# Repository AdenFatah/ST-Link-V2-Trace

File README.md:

# ST-Link-V2-Trace
ST-Link V2 Clone Hardware expanded for Trace Support (SWV/SWO)

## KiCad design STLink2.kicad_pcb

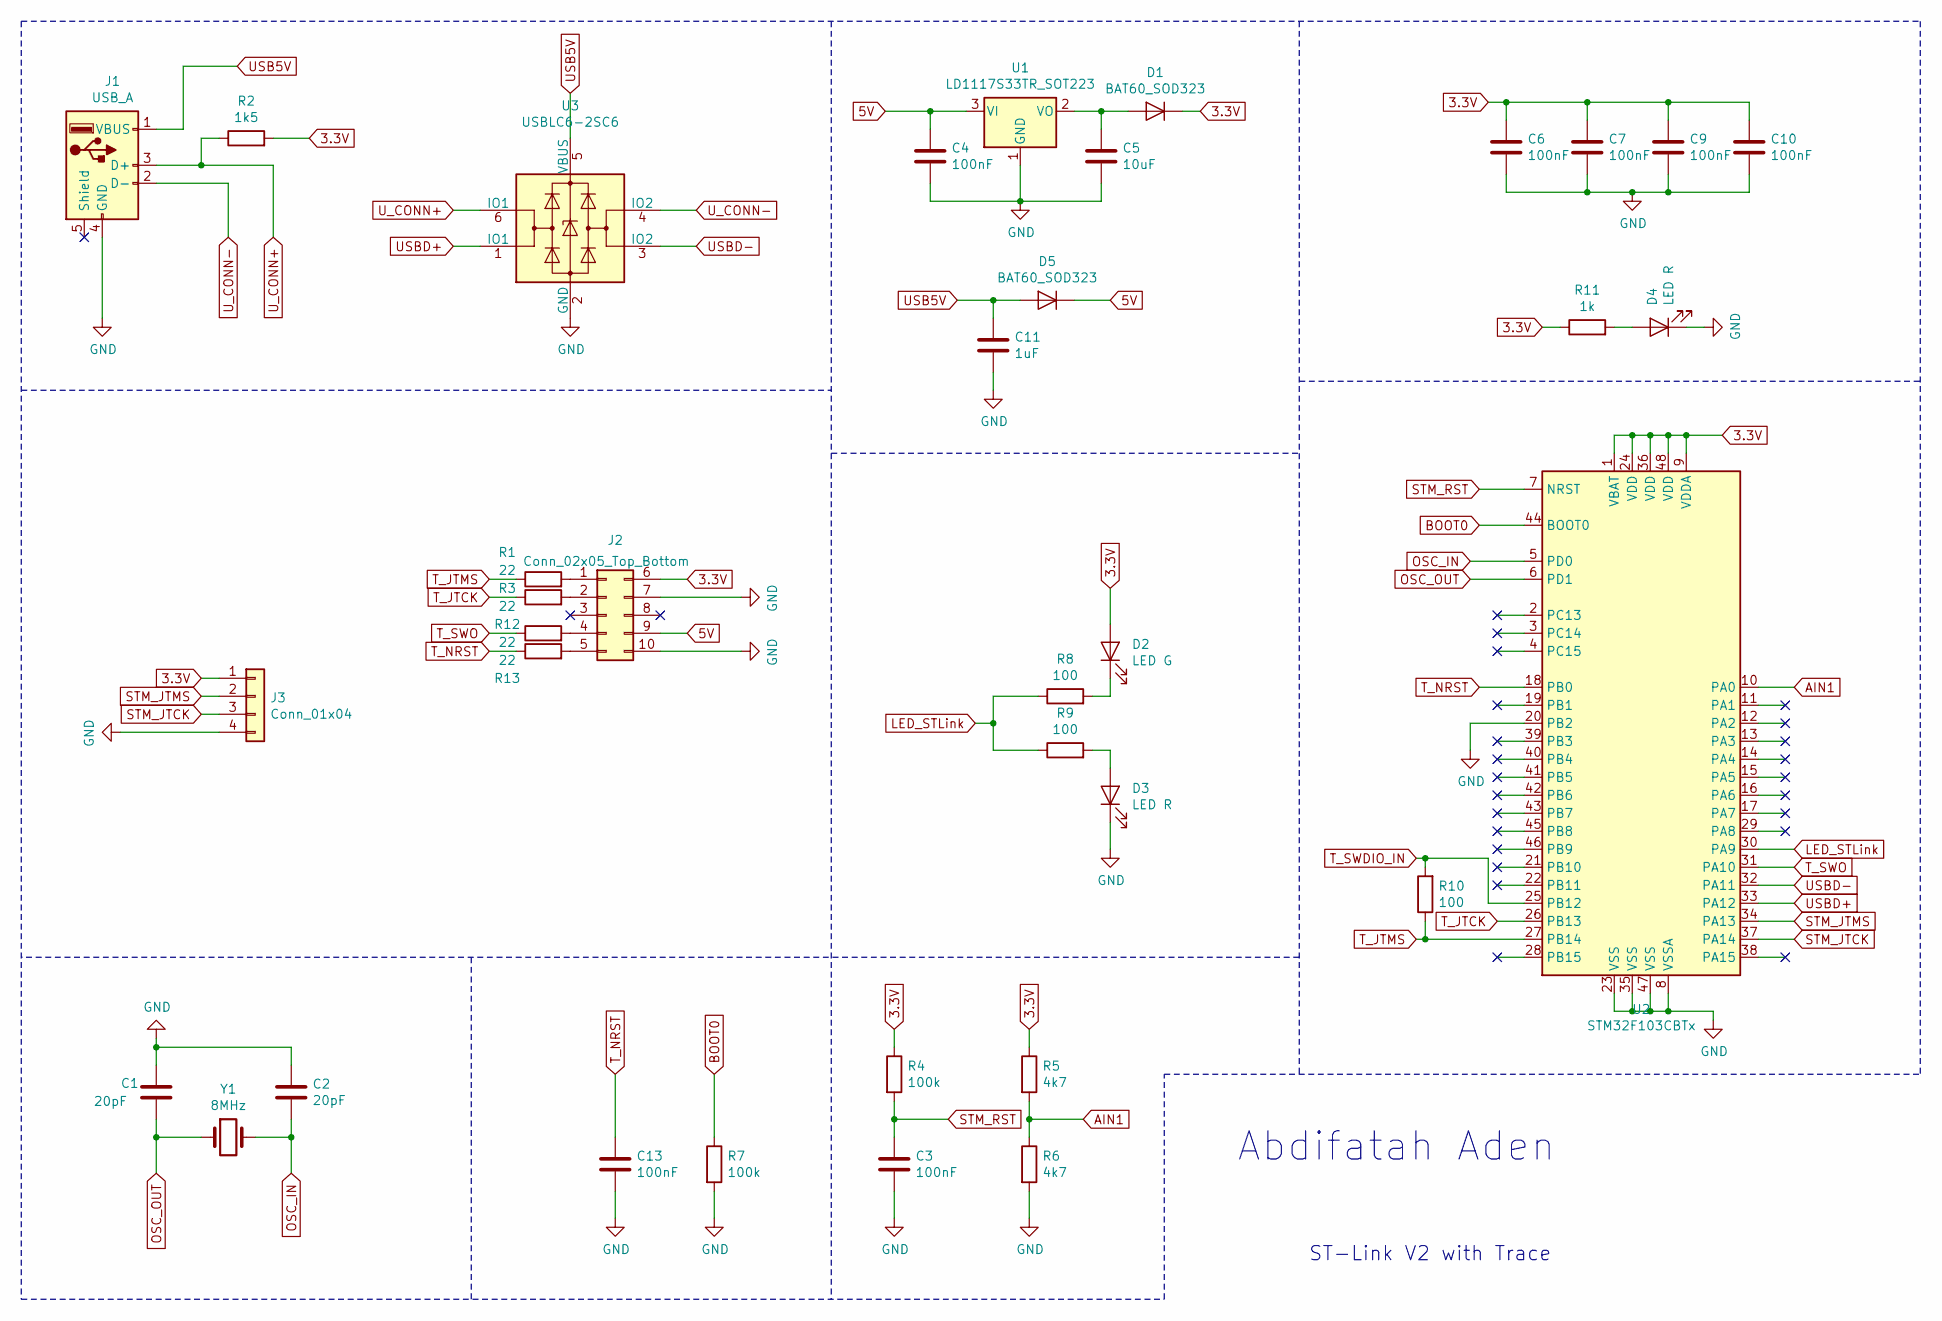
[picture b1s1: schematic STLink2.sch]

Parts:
C1, C2: 20pF; C_0402_1005Metric
C3, C4, C6, C7, C9, C10, C13: 100nF; C_0402_1005Metric
C5: 10uF; C_0402_1005Metric
C11: 1uF; C_0402_1005Metric
D1, D5: BAT60_SOD323; D_SOD-323
D2: LED G; LED_0402_1005Metric
D3, D4: LED R; LED_0402_1005Metric
J1: USB_A; USB_A_CNCTech_1001-011-01101_Horizontal
J2: Conn_02x05_Top_Bottom; Edge_Mount_Connector_10pin
J3: Conn_01x04; JST_EH_B4B-EH-A_1x04_P2.50mm_Vertical
R1, R3, R12, R13: 22; R_0402_1005Metric
R2: 1k5; R_0402_1005Metric
R4, R7: 100k; R_0402_1005Metric
R5, R6: 4k7; R_0402_1005Metric
R8, R9, R10: 100; R_0402_1005Metric
R11: 1k; R_0402_1005Metric
U1: LD1117S33TR_SOT223; SOT-223-3_TabPin2
U2: STM32F103CBTx; LQFP-48_7x7mm_P0.5mm
U3: USBLC6-2SC6; SOT-23-6
Y1: 8MHz; Crystal_SMD_HC49-SD

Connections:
3.3V: C6.1, C7.1, C9.1, C10.1, D1.1 (K), D2.2 (A), J2.6, J3.1, R2.2, R4.1, R5.1, R11.1, U2.1 (VBAT), U2.9 (VDDA), U2.24 (VDD), U2.36 (VDD), U2.48 (VDD)
5V: C4.1, D5.1 (K), J2.9, U1.3 (VI)
AIN1: R5.2, R6.1, U2.10 (PA0)
BOOT0: R7.1, U2.44 (BOOT0)
GND: C1.1, C2.1, C3.2, C4.2, C5.2, C6.2, C7.2, C9.2, C10.2, C11.2, C13.2, D3.1 (K), D4.1 (K), J1.4 (GND), J2.7, J2.10, J3.4, R6.2, R7.2, U1.1 (GND), U2.8 (VSSA), U2.20 (PB2), U2.23 (VSS), U2.35 (VSS), U2.47 (VSS), U3.2 (GND)
LED_STLink: R8.1, R9.1, U2.30 (PA9)
unnamed: C5.1, D1.2 (A), U1.2 (VO)
unnamed: D2.1 (K), R8.2
unnamed: D3.2 (A), R9.2
unnamed: D4.2 (A), R11.2
unnamed: J2.1, R1.2
unnamed: J2.2, R3.2
unnamed: J2.4, R12.2
unnamed: J2.5, R13.2
OSC_IN: C2.2, U2.5 (PD0), Y1.2
OSC_OUT: C1.2, U2.6 (PD1), Y1.1
STM_JTCK: J3.3, U2.37 (PA14)
STM_JTMS: J3.2, U2.34 (PA13)
STM_RST: C3.1, R4.2, U2.7 (NRST)
T_JTCK: R3.1, U2.26 (PB13)
T_JTMS: R1.1, R10.1, U2.27 (PB14)
T_NRST: C13.1, R13.1, U2.18 (PB0)
T_SWDIO_IN: R10.2, U2.25 (PB12)
T_SWO: R12.1, U2.31 (PA10)
USB5V: C11.1, D5.2 (A), J1.1 (VBUS), U3.5 (VBUS)
USBD+: U2.33 (PA12), U3.1 (IO1)
USBD-: U2.32 (PA11), U3.3 (IO2)
U_CONN+: J1.3 (D+), R2.1, U3.6 (IO1)
U_CONN-: J1.2 (D-), U3.4 (IO2)

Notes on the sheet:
Abdifatah Aden
ST-Link V2 with Trace

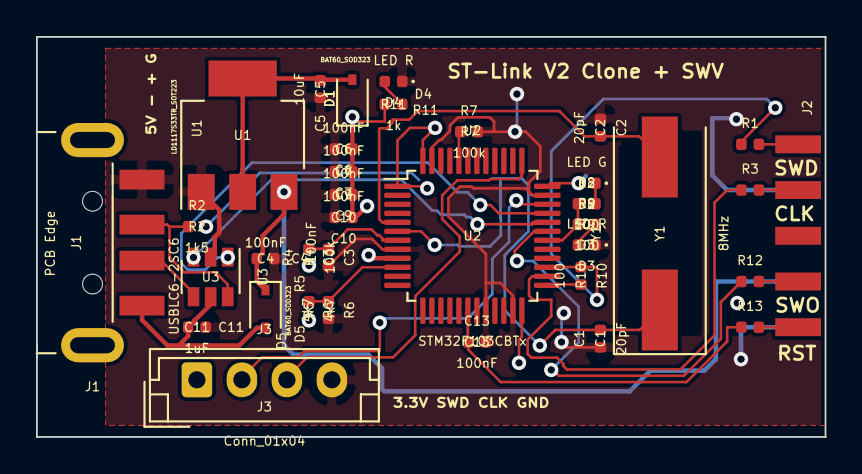
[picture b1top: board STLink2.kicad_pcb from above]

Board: 2 copper layers, 43.8 x 22.2 mm, 36 parts (0 on the bottom side), 29 nets.

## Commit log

2020-07-22 File
